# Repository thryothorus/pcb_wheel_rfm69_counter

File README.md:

# Wheel Counter, Battery Powered, RFM69 at 433MHz

## Objective
- Monitor how much critters are running on their wheels, at [The Creature Conservancy](http://www.thecreatureconservancy.org/).  Physical activity could correlate with health
- Create a wireless, battery powered, sensing network for additional sensors in the future

## Features
- NFC antenna for quick reading/changing of metadata (i.e. setting the animal name for transmission)
- RTC (Real Time Clock)
- N-MOSFET polarity protection
- Several debug switches
- TagConnect interface
  
### Schematic

### PCB

## What's Next
- Populating PCB
- Writing code

## License: GPLv3 where not covered by other licenses

## Resources
NFC antenna design taken from [Sparkfun's implementation](https://www.sparkfun.com/products/21274)
Footprints from various sources online, including Sparkfun and Adafruit

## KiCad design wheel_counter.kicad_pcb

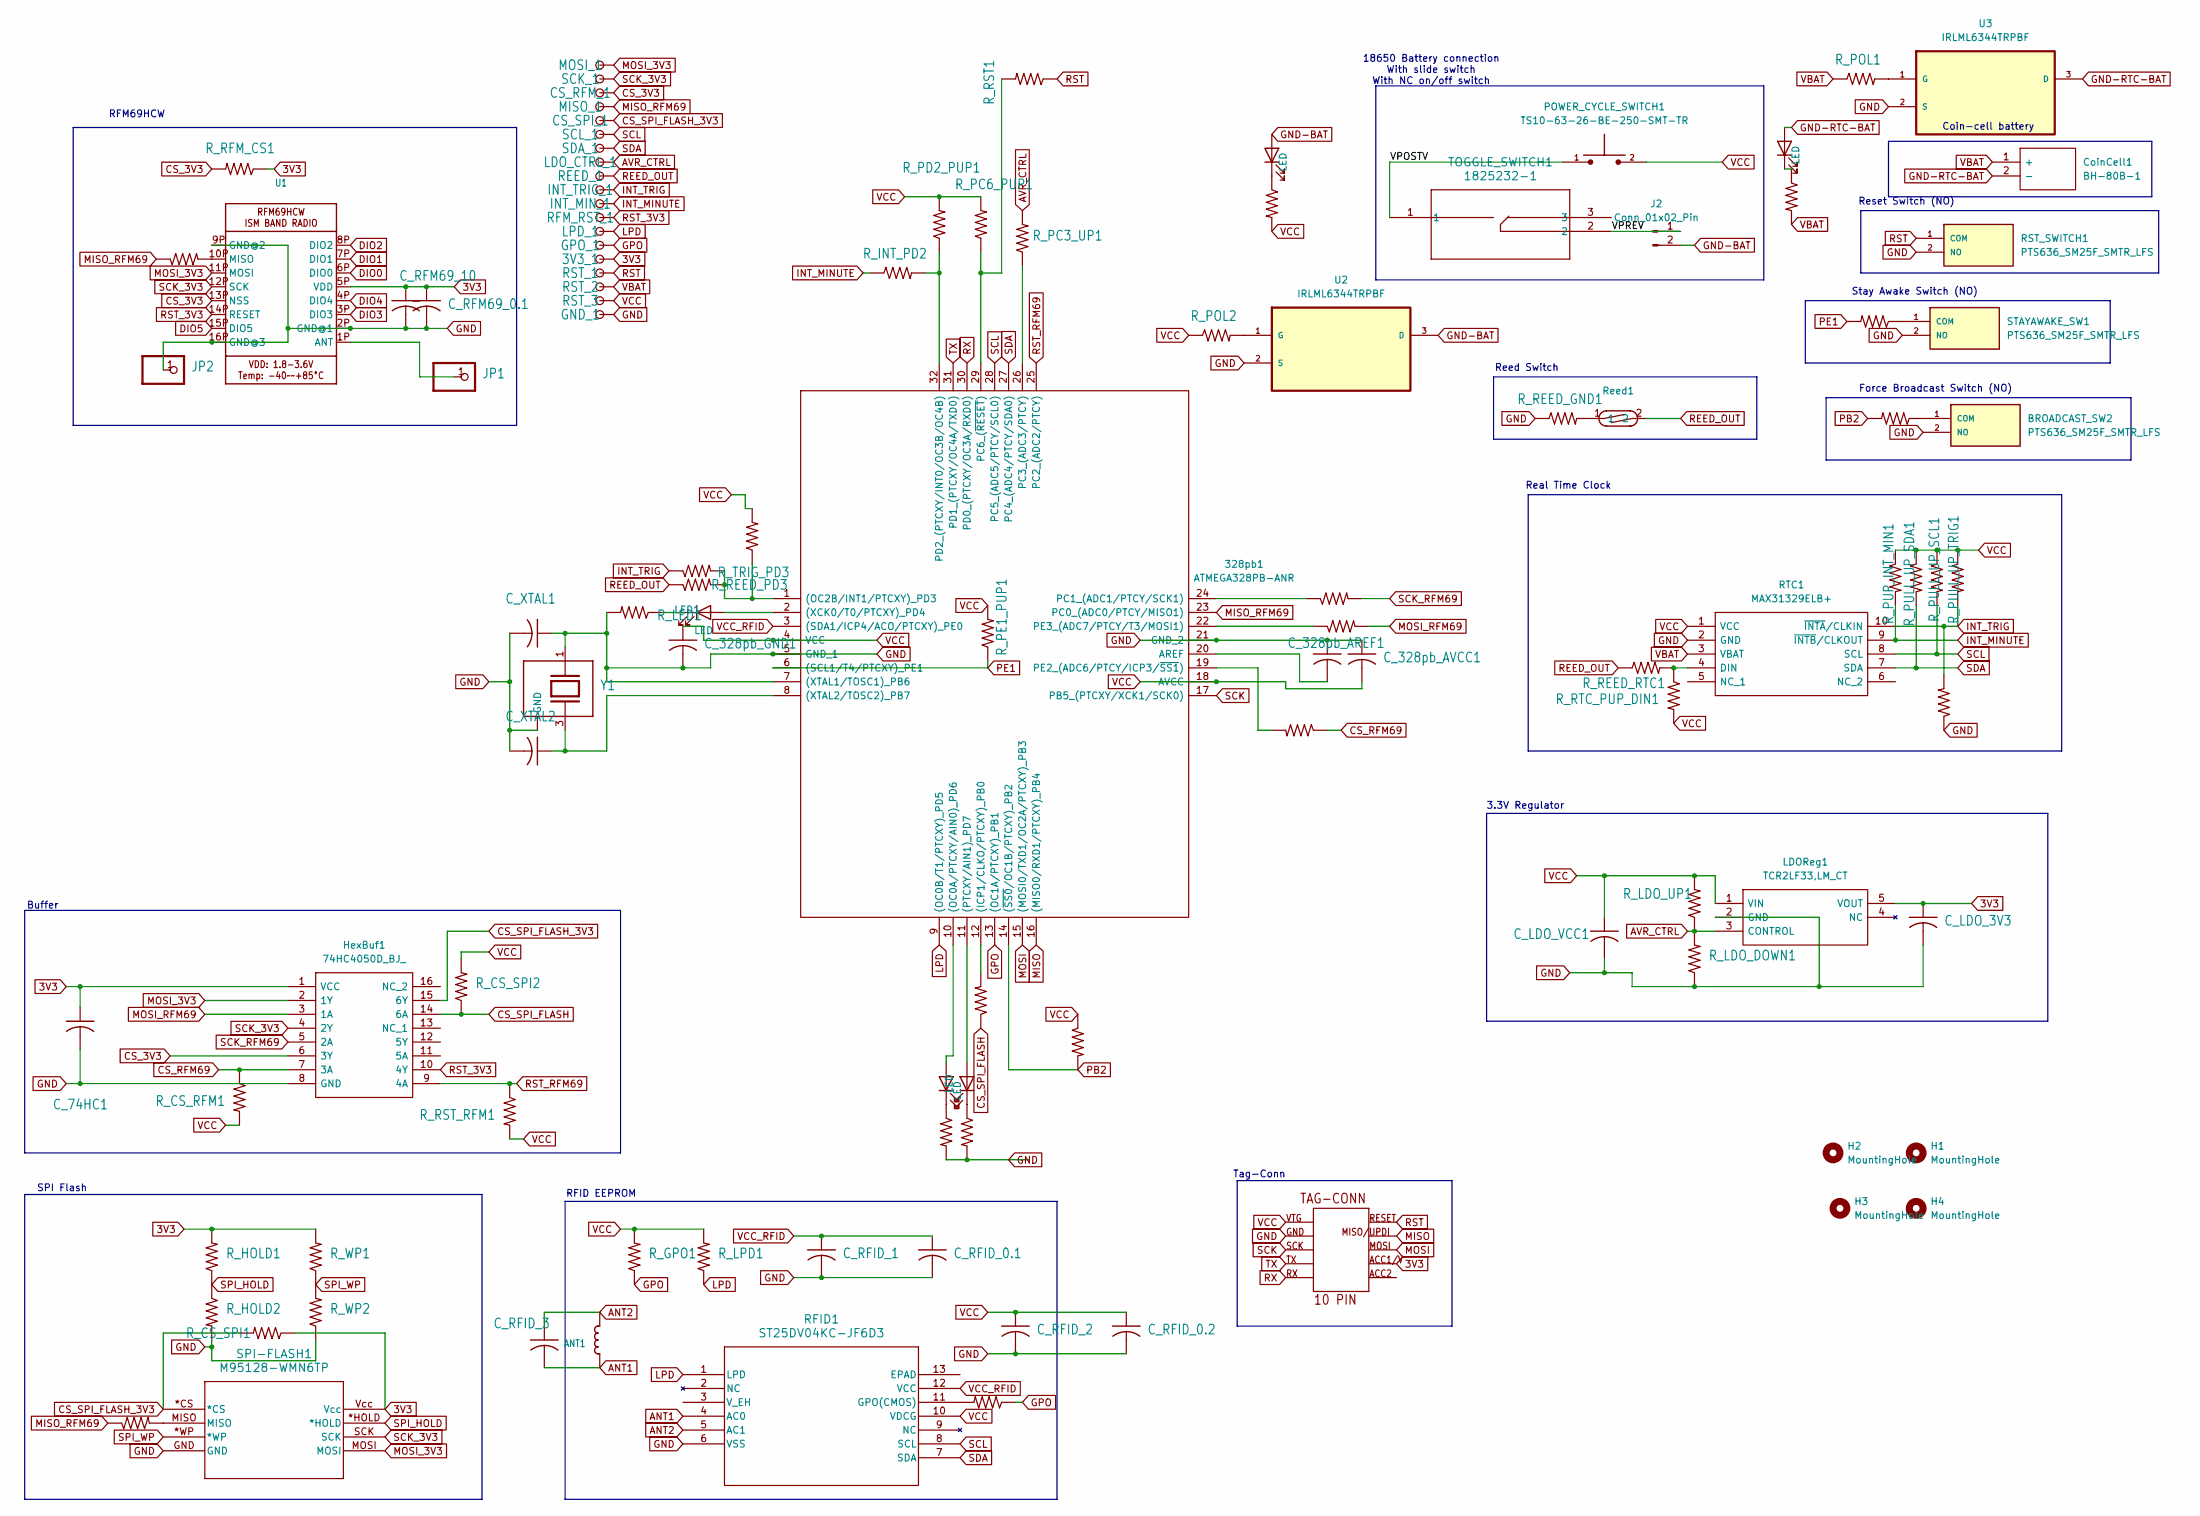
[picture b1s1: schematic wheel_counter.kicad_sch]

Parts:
3V3_1: MOX-OXLEY-TEST-POINT
328pb1: ATMEGA328PB-ANR; QFP80P900X900X120-32N; Manufacturer_Part_Number ATMEGA328PB-ANR; Mouser Part Number 556-ATMEGA328PB-ANR
ANT1: NFCANT_25X15
BROADCAST_SW2: PTS636_SM25F_SMTR_LFS; PTS636SM25FSMTRLFS; Mouser_Part_Number 611-PTS636SM25FSMTRL
CS_RFM_1: MOX-OXLEY-TEST-POINT
CS_SPI_1: MOX-OXLEY-TEST-POINT
C_74HC1, C_328pb_AREF1, C_328pb_AVCC1, C_328pb_GND1: C0805
C_LDO_3V3: C0805
C_LDO_VCC1: C0805
C_RFID_0.1, C_RFID_0.2, C_RFID_1, C_RFID_2, C_RFID_3: C0805
C_RFM69_0.1, C_RFM69_10: C0805
C_XTAL1, C_XTAL2: C0805
CoinCell1: BH-80B-1; BH80B1; Manufacturer_Part_Number BH-80B-1
GND_1: MOX-OXLEY-TEST-POINT
GPO_1: MOX-OXLEY-TEST-POINT
H1, H2, H3, H4: MountingHole; MountingHole_3.2mm_M3
HexBuf1: 74HC4050D_BJ_; SOIC127P600X175-16N; Manufacturer_Part_Number 74HC4050D(BJ); Mouser Part Number 757-74HC4050DBJ
INT_MIN_1: MOX-OXLEY-TEST-POINT
INT_TRIG_1: MOX-OXLEY-TEST-POINT
J2: Conn_01x02_Pin; PinHeader_1x02_P2.54mm_Vertical
JP1, JP2: 1X01_ROUND
LDOReg1: TCR2LF33,LM_CT; TCR2LF33LMCT; Manufacturer_Part_Number TCR2LF33,LM(CT; Mouser Part Number 757-TCR2LF33LMCT
LDO_CTRL_1: MOX-OXLEY-TEST-POINT
LED1, LED2, LED3, LED4, LED5: LED; LED_0805_2012Metric_Pad1.15x1.40mm_HandSolder
LPD_1: MOX-OXLEY-TEST-POINT
MISO_1: MOX-OXLEY-TEST-POINT
MOSI_1: MOX-OXLEY-TEST-POINT
POWER_CYCLE_SWITCH1: TS10-63-26-BE-250-SMT-TR; SW_TS10-63-26-BE-250-SMT-TR; PARTREV 1.0
REED_1: MOX-OXLEY-TEST-POINT
RFID1: ST25DV04KC-JF6D3; UFDFPN12_ST25DV_STM
RFM_RST_1: MOX-OXLEY-TEST-POINT
RST_1, RST_2, RST_3: MOX-OXLEY-TEST-POINT
RST_SWITCH1: PTS636_SM25F_SMTR_LFS; PTS636SM25FSMTRLFS; Mouser_Part_Number 611-PTS636SM25FSMTRL
RTC1: MAX31329ELB+; MAX31329ELB; Manufacturer_Part_Number MAX31329ELB+; Mouser Part Number 700-MAX31329ELB+
R_CS_RFM1, R_CS_RFM2: R0805
R_CS_SPI1, R_CS_SPI2, R_CS_SPI3, R_CS_SPI4: R0805
R_GPO1, R_GPO2: R0805
R_HOLD1, R_HOLD2: R0805
R_INT_PD2: R0805
R_LDO_DOWN1: R0805
R_LDO_UP1: R0805
R_LED1, R_LED2, R_LED3, R_LED4, R_LED5: R0805
R_LPD1: R0805
R_MISO_RFM1: R0805
R_MISO_SPI1: R0805
R_MOSI1: R0805
R_PC3_UP1, R_PC6_PUP1: R0805
R_PD2_PUP1, R_PD3_UP1: R0805
R_PE1, R_PE1_PUP1, R_PE2: R0805
R_POL1, R_POL2: R0805
R_PULL_DOWN_TRIG1: R0805
R_PULL_UP_SCL1: R0805
R_PULL_UP_SDA1: R0805
R_PULL_UP_TRIG1: R0805
R_PUP_INT_MIN1: R0805
R_REED_GND1: R0805
R_REED_PD3: R0805
R_REED_RTC1: R0805
R_RFM_CS1: R0805
R_RST1: R0805
R_RST_RFM1: R0805
R_RTC_PUP_DIN1: R0805
R_SCK1: R0805
R_TRIG_PD3: R0805
R_WP1, R_WP2: R0805
Reed1: MDSM-4_15.3mm_Surface_Mount_Reed_Switch
SCK_1: MOX-OXLEY-TEST-POINT
SCL_1: MOX-OXLEY-TEST-POINT
SDA_1: MOX-OXLEY-TEST-POINT
SPI-FLASH1: M95128-WMN6TP; SO-8_STM
STAYAWAKE_SW1: PTS636_SM25F_SMTR_LFS; PTS636SM25FSMTRLFS; Mouser_Part_Number 611-PTS636SM25FSMTRL
TAGCONN1: TAG-CONNECT_TC2050-IDC-NL-CUSTOM
TOGGLE_SWITCH1: 1825232-1; 1825232-1_TEC
U1: RFMHCW_SMT
U2, U3: IRLML6344TRPBF; SOT95P240X112-3N; MPN IRLML6344TRPBF
Y1: XTAL_TSX-3225_16.0000MF18X-AC0

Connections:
3V3: 3V3_1.1, C_74HC1.1, C_LDO_3V3.1, C_RFM69_0.1.1, C_RFM69_10.1, HexBuf1.1 (VCC), LDOReg1.5 (VOUT), R_CS_SPI1.1, R_HOLD1.2, R_RFM_CS1.1, R_WP1.2, SPI-FLASH1.Vcc, TAGCONN1.ACC1/V, U1.5P (VDD)
/VPOSTV: POWER_CYCLE_SWITCH1.1, TOGGLE_SWITCH1.1
/VPREV: J2.1, TOGGLE_SWITCH1.2
ANT1: ANT1.IN2 (1), ANT1.P$1 (1), C_RFID_3.2, RFID1.4 (AC0)
ANT2: ANT1.IN1 (2), ANT1.P$2 (2), C_RFID_3.1, RFID1.5 (AC1)
AVR_CTRL: LDOReg1.3 (CONTROL), LDO_CTRL_1.1, R_LDO_DOWN1.2, R_LDO_UP1.1, R_PC3_UP1.2
CS_3V3: CS_RFM_1.1, HexBuf1.6 (3Y), R_RFM_CS1.2, U1.13P (NSS)
CS_RFM69: HexBuf1.7 (3A), R_CS_RFM1.1, R_CS_RFM2.1
CS_SPI_FLASH: HexBuf1.14 (6A), R_CS_SPI2.1, R_CS_SPI3.1
CS_SPI_FLASH_3V3: CS_SPI_1.1, HexBuf1.15 (6Y), R_CS_SPI1.2, SPI-FLASH1.*CS
DIO0: U1.6P (DIO0)
DIO1: U1.7P (DIO1)
DIO2: U1.8P (DIO2)
DIO3: U1.3P (DIO3)
DIO4: U1.4P (DIO4)
DIO5: U1.15P (DIO5)
GND: 328pb1.5 (GND_1), 328pb1.7 ((XTAL1/TOSC1)_PB6), 328pb1.21 (GND_2), BROADCAST_SW2.2 (NO), C_74HC1.2, C_328pb_AREF1.1, C_328pb_AVCC1.1, C_328pb_GND1.2, C_LDO_3V3.2, C_LDO_VCC1.2, C_RFID_0.1.2, C_RFID_0.2.2, C_RFID_1.2, C_RFID_2.2, C_RFM69_0.1.2, C_RFM69_10.2, C_XTAL1.1, C_XTAL1.2, C_XTAL2.2, GND_1.1, HexBuf1.8 (GND), JP2.1, LDOReg1.2 (GND), RFID1.6 (VSS), RST_SWITCH1.2 (NO), RTC1.2 (GND), R_HOLD2.2, R_LDO_DOWN1.1, R_LED1.2, R_LED2.2, R_LED3.2, R_PULL_DOWN_TRIG1.1, R_REED_GND1.1, R_WP2.1, SPI-FLASH1.GND, STAYAWAKE_SW1.2 (NO), TAGCONN1.GND, U1.2P (GND@1), U1.9P (GND@2), U1.16P (GND@3), U2.2 (S), U3.2 (S), Y1.1, Y1.2 (GND), Y1.4 (GND)
GND-BAT: J2.2, LED4.2 (A), U2.3 (D)
GND-RTC-BAT: CoinCell1.2 (-), LED5.2 (A), U3.3 (D)
GPO: 328pb1.13 ((OC1A/PTCXY)_PB1), GPO_1.1, R_GPO1.1, R_GPO2.1
INT_MINUTE: INT_MIN_1.1, RTC1.9 (~INTB/CLKOUT), R_INT_PD2.1, R_PUP_INT_MIN1.2
INT_TRIG: INT_TRIG_1.1, RTC1.10 (~INTA/CLKIN), R_PULL_DOWN_TRIG1.2, R_PULL_UP_TRIG1.2, R_TRIG_PD3.1
LPD: 328pb1.9 ((OC0B/T1/PTCXY)_PD5), LPD_1.1, RFID1.1 (LPD), R_LPD1.1
MISO: 328pb1.16 ((MISO0/RXD1/PTCXY)_PB4), TAGCONN1.MISO/UPDI
MISO_RFM69: 328pb1.23 (PC0_(ADC0/PTCY/MISO1)), MISO_1.1, R_MISO_RFM1.1, R_MISO_SPI1.1
MOSI: 328pb1.15 ((MOSI0/TXD1/OC2A/PTCXY)_PB3), TAGCONN1.MOSI
MOSI_3V3: HexBuf1.2 (1Y), MOSI_1.1, SPI-FLASH1.MOSI, U1.11P (MOSI)
MOSI_RFM69: HexBuf1.3 (1A), R_MOSI1.2
unnamed: 328pb1.12 ((ICP1/CLKO/PTCXY)_PB0), R_CS_SPI3.2
unnamed: 328pb1.10 ((OC0A/PTCXY/AIN0)_PD6), LED2.2 (A)
unnamed: 328pb1.1 ((OC2B/INT1/PTCXY)_PD3), R_PD3_UP1.1, R_REED_PD3.2, R_TRIG_PD3.2
unnamed: 328pb1.11 ((PTCXY/AIN1)_PD7), LED3.2 (A)
unnamed: 328pb1.2 ((XCK0/T0/PTCXY)_PD4), LED1.2 (A)
unnamed: 328pb1.8 ((XTAL2/TOSC2)_PB7), C_XTAL2.1, Y1.3 (2)
unnamed: 328pb1.20 (AREF), C_328pb_AREF1.2
unnamed: 328pb1.24 (PC1_(ADC1/PTCY/SCK1)), R_SCK1.1
unnamed: 328pb1.26 (PC3_(ADC3/PTCY)), R_PC3_UP1.1
unnamed: 328pb1.29 (PC6_(~RESET)), R_PC6_PUP1.1, R_RST1.2
unnamed: 328pb1.32 (PD2_(PTCXY/INT0/OC3B/OC4B)), R_INT_PD2.2, R_PD2_PUP1.1
unnamed: 328pb1.19 (PE2_(ADC6/PTCY/ICP3/~SS1)), R_CS_RFM2.2
unnamed: 328pb1.22 (PE3_(ADC7/PTCY/T3/MOSI1)), R_MOSI1.1
unnamed: BROADCAST_SW2.1 (COM), R_PE2.1
unnamed: LED1.1 (K), R_LED1.1
unnamed: LED2.1 (K), R_LED2.1
unnamed: LED3.1 (K), R_LED3.1
unnamed: LED4.1 (K), R_LED4.1
unnamed: LED5.1 (K), R_LED5.1
unnamed: RFID1.11 (GPO(CMOS)), R_GPO2.2
unnamed: RTC1.4 (DIN), R_REED_RTC1.2, R_RTC_PUP_DIN1.1
unnamed: R_MISO_SPI1.2, SPI-FLASH1.MISO
unnamed: R_REED_GND1.2, Reed1.1
unnamed: R_PE1.1, STAYAWAKE_SW1.1 (COM)
unnamed: JP1.1, U1.1P (ANT)
unnamed: R_MISO_RFM1.2, U1.10P (MISO)
unnamed: R_POL2.2, U2.1 (G)
unnamed: R_POL1.2, U3.1 (G)
PB2: 328pb1.14 ((~SS0/OC1B/PTCXY)_PB2), R_CS_SPI4.2, R_PE2.2
PE1: 328pb1.6 ((SCL1/T4/PTCXY)_PE1), R_PE1.2, R_PE1_PUP1.1
REED_OUT: REED_1.1, R_REED_PD3.1, R_REED_RTC1.1, Reed1.2
RST: RST_1.1, RST_SWITCH1.1 (COM), R_RST1.1, TAGCONN1.RST (RESET)
RST_3V3: HexBuf1.10 (4Y), RFM_RST_1.1, U1.14P (RESET)
RST_RFM69: 328pb1.25 (PC2_(ADC2/PTCY)), HexBuf1.9 (4A), R_RST_RFM1.1
RX: 328pb1.30 (PD0_(PTCXY/OC3A/RXD0)), TAGCONN1.RX
SCK: 328pb1.17 (PB5_(PTCXY/XCK1/SCK0)), TAGCONN1.SCK
SCK_3V3: HexBuf1.4 (2Y), SCK_1.1, SPI-FLASH1.SCK, U1.12P (SCK)
SCK_RFM69: HexBuf1.5 (2A), R_SCK1.2
SCL: 328pb1.28 (PC5_(ADC5/PTCY/SCL0)), RFID1.8 (SCL), RTC1.8 (SCL), R_PULL_UP_SCL1.2, SCL_1.1
SDA: 328pb1.27 (PC4_(ADC4/PTCY/SDA0)), RFID1.7 (SDA), RTC1.7 (SDA), R_PULL_UP_SDA1.2, SDA_1.1
SPI_HOLD: R_HOLD1.1, R_HOLD2.1, SPI-FLASH1.*HOLD
SPI_WP: R_WP1.1, R_WP2.2, SPI-FLASH1.*WP
TX: 328pb1.31 (PD1_(PTCXY/OC4A/TXD0)), TAGCONN1.TX
VBAT: CoinCell1.1 (+), RST_2.1, RTC1.3 (VBAT), R_LED5.2, R_POL1.1; also elsewhere on the board
VCC: 328pb1.4 (VCC), 328pb1.18 (AVCC), C_328pb_AVCC1.2, C_328pb_GND1.1, C_LDO_VCC1.1, C_RFID_0.2.1, C_RFID_2.1, LDOReg1.1 (VIN), POWER_CYCLE_SWITCH1.2, RFID1.10 (VDCG), RST_3.1, RTC1.1 (VCC), R_CS_RFM1.2, R_CS_SPI2.2, R_CS_SPI4.1, R_GPO1.2, R_LDO_UP1.2, R_LED4.2, R_LPD1.2, R_PC6_PUP1.2, R_PD2_PUP1.2, R_PD3_UP1.2, R_PE1_PUP1.2, R_POL2.1, R_PULL_UP_SCL1.1, R_PULL_UP_SDA1.1, R_PULL_UP_TRIG1.1, R_PUP_INT_MIN1.1, R_RST_RFM1.2, R_RTC_PUP_DIN1.2, TAGCONN1.VTG; also elsewhere on the board
VCC_RFID: 328pb1.3 ((SDA1/ICP4/ACO/PTCXY)_PE0), C_RFID_0.1.1, C_RFID_1.1, RFID1.12 (VCC)

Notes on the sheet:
RFID EEPROM
RFM69HCW
Tag-Conn
Force Broadcast Switch (NO)
Buffer
Reset Switch (NO)
Real Time Clock
Coin-cell battery
SPI Flash
18650 Battery connection With slide switch With NC on/off switch
Reed Switch
3.3V Regulator
Stay Awake Switch (NO)

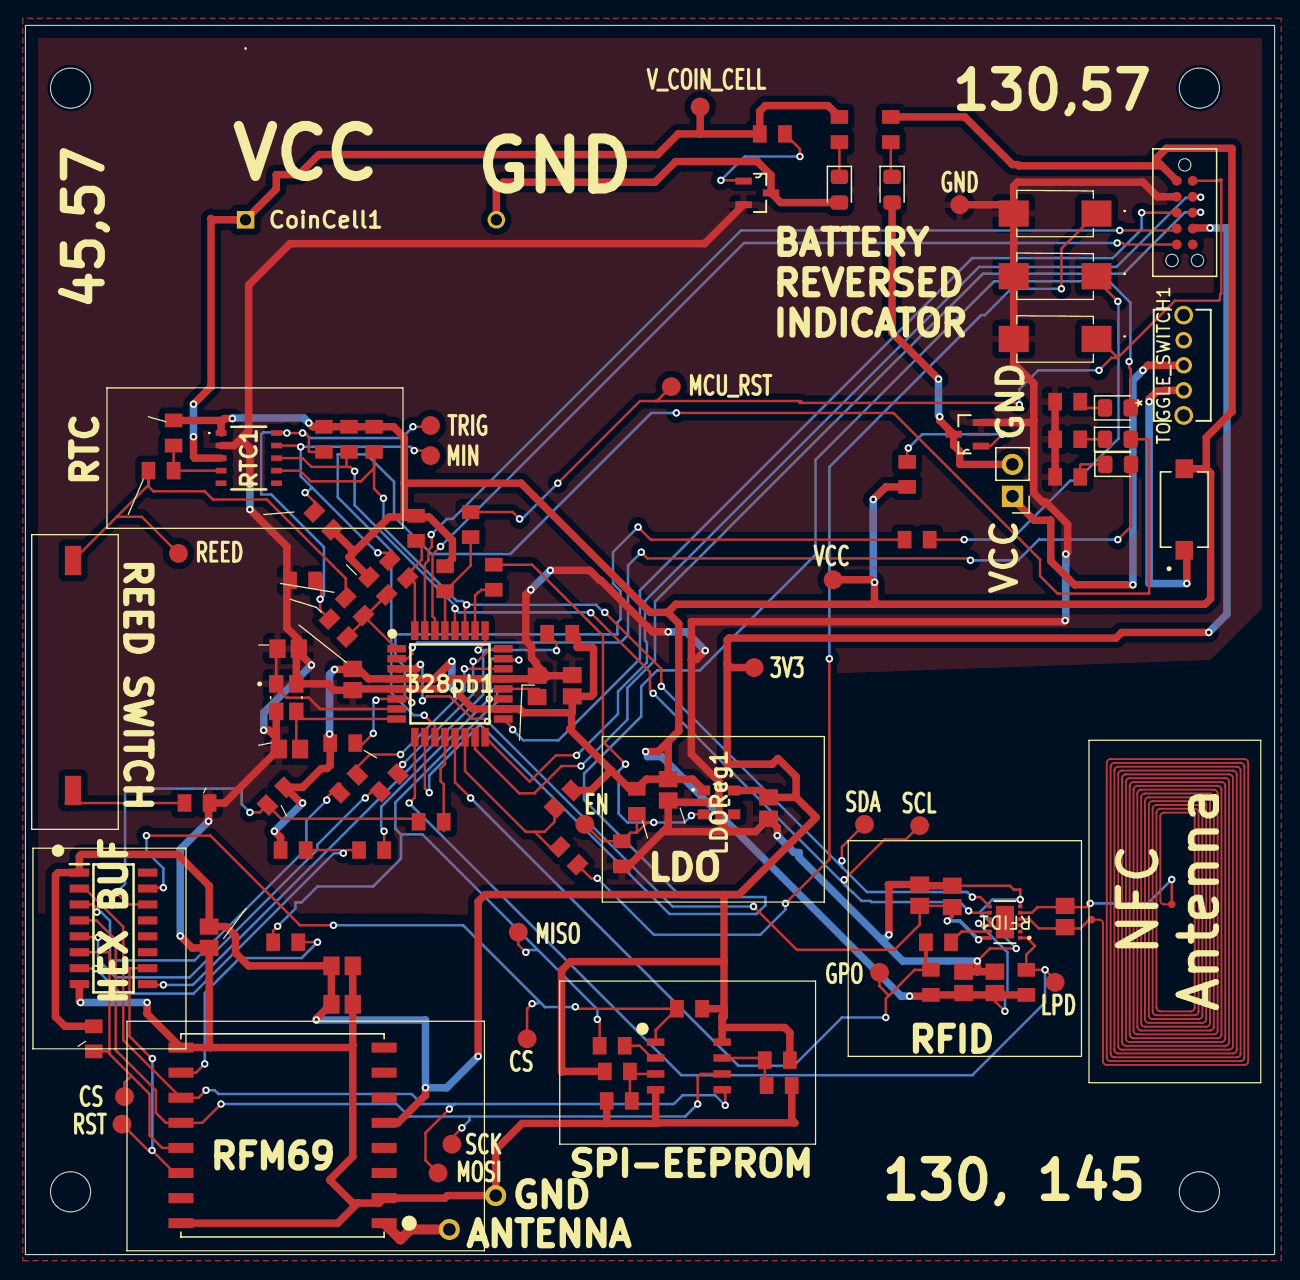
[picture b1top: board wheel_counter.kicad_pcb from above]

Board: 2 copper layers, 99.6 x 98.0 mm, 112 parts (0 on the bottom side), 68 nets.

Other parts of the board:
VBAT_1: MOX-OXLEY-TEST-POINT
VCC_1: MOX-OXLEY-TEST-POINT

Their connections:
VBAT: VBAT_1.1; also elsewhere on the board
VCC: VCC_1.1; also elsewhere on the board

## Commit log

2024-11-25 initial push
2024-11-25 added pictures of pcb and schematic
2024-11-25 Filling in Readme.md
2024-12-18 fix ground
2024-12-18 moved to pcb folder
2024-12-18 added code
2024-12-18 moved code
2025-01-29 bump
